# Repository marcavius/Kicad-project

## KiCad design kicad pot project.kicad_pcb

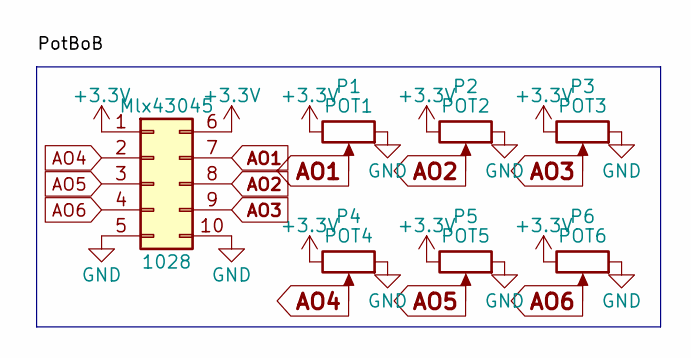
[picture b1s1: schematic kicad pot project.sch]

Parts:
Mlx43045: 1028; Molex_Microfit3_Header_02x05_Straight_43045-1028
P1: POT1; Potentiometer_Alps_RK09K_Horizontal
P2: POT2; Potentiometer_Alps_RK09K_Horizontal
P3: POT3; Potentiometer_Alps_RK09K_Horizontal
P4: POT4; Potentiometer_Alps_RK09K_Horizontal
P5: POT5; Potentiometer_Alps_RK09K_Horizontal
P6: POT6; Potentiometer_Alps_RK09K_Horizontal

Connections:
+3V3: Mlx43045.1, Mlx43045.6, P1.3, P2.3, P3.3, P4.3, P5.3, P6.3
AO1: Mlx43045.7, P1.2
AO2: Mlx43045.8, P2.2
AO3: Mlx43045.9, P3.2
AO4: Mlx43045.2, P4.2
AO5: Mlx43045.3, P5.2
AO6: Mlx43045.4, P6.2
GND: Mlx43045.5, Mlx43045.10, P1.1, P2.1, P3.1, P4.1, P5.1, P6.1

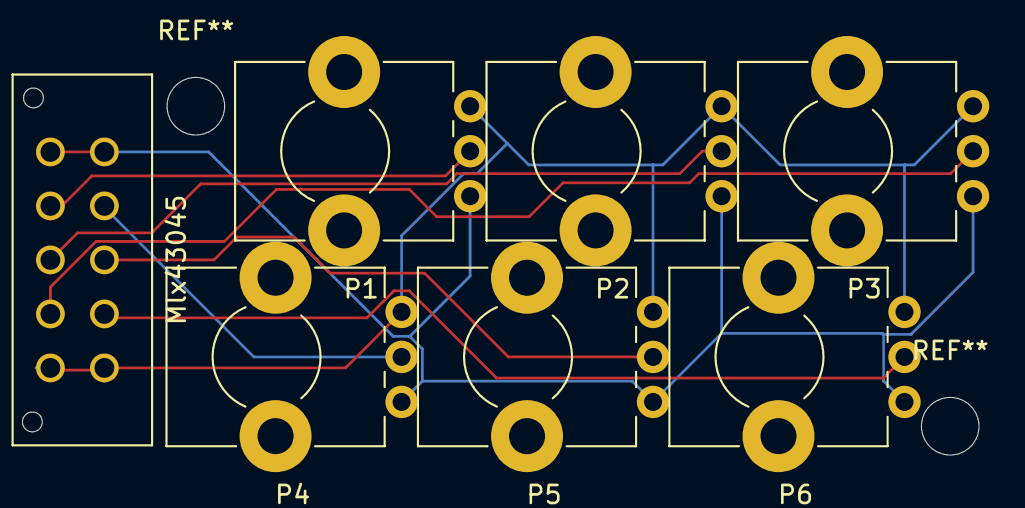
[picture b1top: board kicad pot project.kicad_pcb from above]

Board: 2 copper layers, 7 parts (0 on the bottom side), 8 nets.

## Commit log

2018-01-25 Kicad project
    DOing a pot board
